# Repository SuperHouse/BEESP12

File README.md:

BeeSP12 ESP8266 Module
======================
Copyright 2016 SuperHouse Automation Pty Ltd  www.superhouse.tv  

An ESP8266 module with an XBee footprint, using an ESP-12.

Features:

 * XBee footprint
 * ESP8266 MCU

INSTALLATION
------------
The design is saved as an EAGLE project. EAGLE PCB design software is
available from www.cadsoftusa.com free for non-commercial use. To use
this project download it and place the directory containing these files
into the "eagle" directory on your computer. Then open EAGLE and
navigate to the project.

CREDITS
-------
Designed by Jonathan Oxer jon@oxer.com.au

DISTRIBUTION
------------
The specific terms of distribution of this project are governed by the
license referenced below.

LICENSE
-------
Licensed under the TAPR Open Hardware License (www.tapr.org/OHL).
The "license" folder within this repository also contains a copy of
this license in plain text format.

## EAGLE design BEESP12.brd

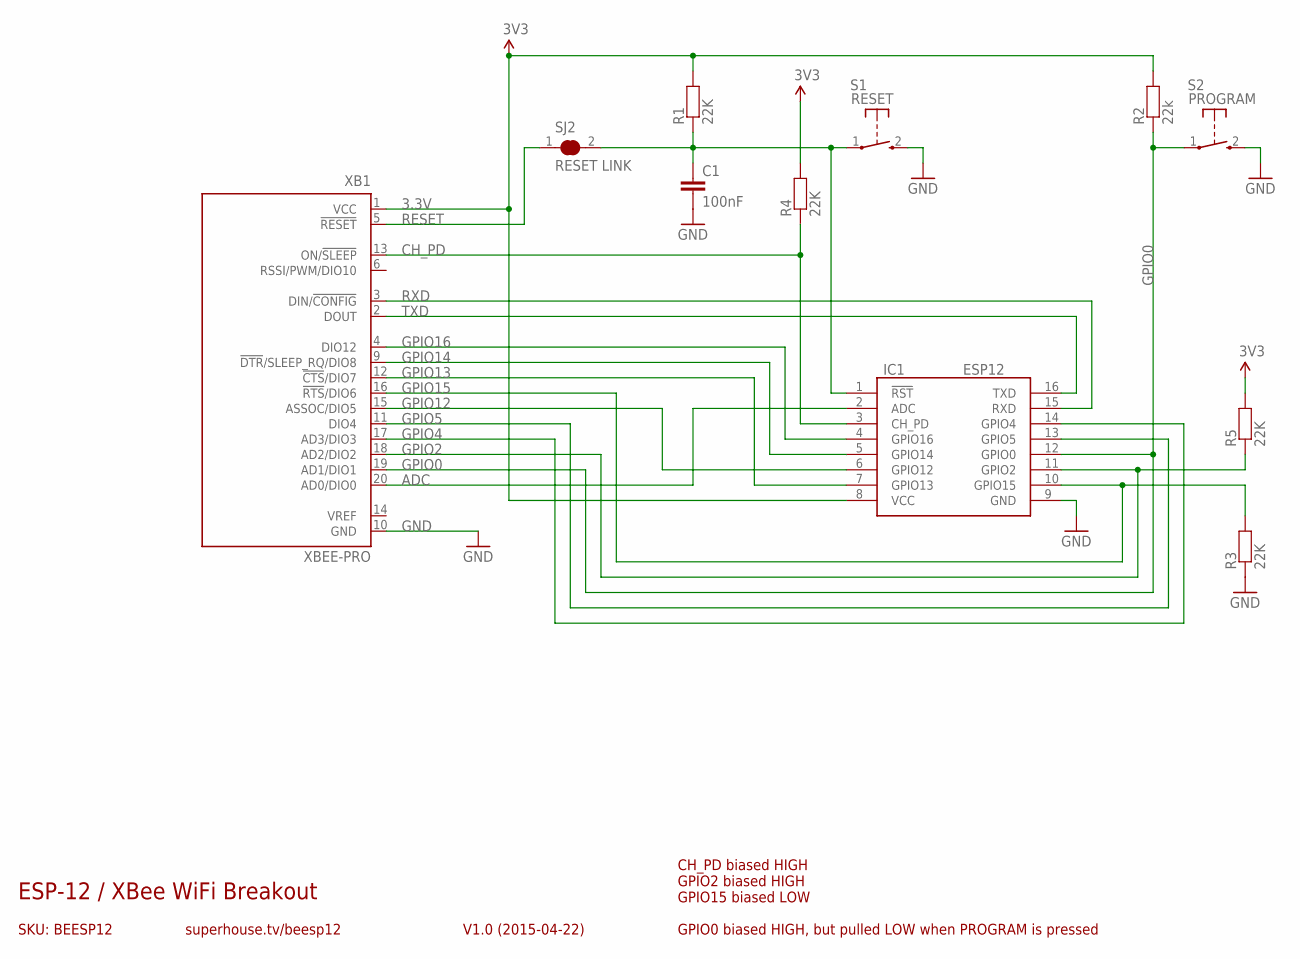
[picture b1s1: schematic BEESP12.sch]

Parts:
C1: 100nF; 0603
IC1: ESP12
R1, R3, R4, R5: 22K; 0603
R2: 22k; 0603
S1: RESET; TACTILE_SWITCH_SMD_2PIN_TINY
S2: PROGRAM; TACTILE_SWITCH_SMD_2PIN_TINY
SJ2: RESET LINK; SJC
XB1: XBEE-PRO

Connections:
3.3V: IC1.8 (VCC), R1.2, R2.2, R4.2, R5.2, XB1.1 (VCC)
ADC: IC1.2 (ADC), XB1.20 (AD0/DIO0)
CH_PD: IC1.3 (CH_PD), R4.1, XB1.13 (ON/!SLEEP)
GND: C1.2, IC1.9 (GND), R3.1, S1.2 (S), S2.2 (S), XB1.10 (GND)
GPIO0: IC1.12 (GPIO0), R2.1, S2.1, XB1.19 (AD1/DIO1)
GPIO2: IC1.11 (GPIO2), R5.1, XB1.18 (AD2/DIO2)
GPIO4: IC1.14 (GPIO4), XB1.17 (AD3/DIO3)
GPIO5: IC1.13 (GPIO5), XB1.11 (DIO4)
GPIO12: IC1.6 (GPIO12), XB1.15 (ASSOC/DIO5)
GPIO13: IC1.7 (GPIO13), XB1.12 (!CTS!/DIO7)
GPIO14: IC1.5 (GPIO14), XB1.9 (!DTR!/SLEEP_RQ/DIO8)
GPIO15: IC1.10 (GPIO15), R3.2, XB1.16 (!RTS!/DIO6)
GPIO16: IC1.4 (GPIO16), XB1.4 (DIO12)
unnamed: C1.1, IC1.1 (!RST), R1.1, S1.1, SJ2.2
RESET: SJ2.1, XB1.5 (!RESET)
RXD: IC1.15 (RXD), XB1.3 (DIN/!CONFIG)
TXD: IC1.16 (TXD), XB1.2 (DOUT)

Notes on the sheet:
SKU: BEESP12
ESP-12 / XBee WiFi Breakout
V1.0 (2015-04-22)
superhouse.tv/beesp12
CH_PD biased HIGH GPIO2 biased HIGH GPIO15 biased LOW GPIO0 biased HIGH, but pulled LOW when PROGRAM is pressed

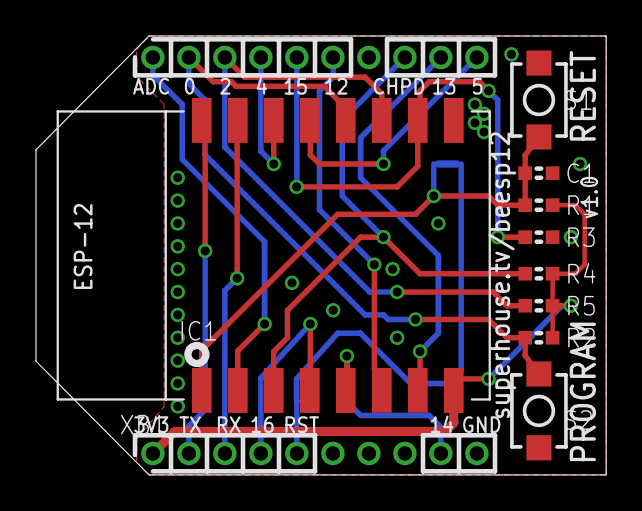
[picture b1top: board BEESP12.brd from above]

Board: 2 copper layers, 31.7 x 24.4 mm, 11 parts (1 on the bottom side), 17 nets.

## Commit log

2015-04-23 Initial project import

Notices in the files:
BEESP12.brd:
(c)2015 Superhouse Automation
